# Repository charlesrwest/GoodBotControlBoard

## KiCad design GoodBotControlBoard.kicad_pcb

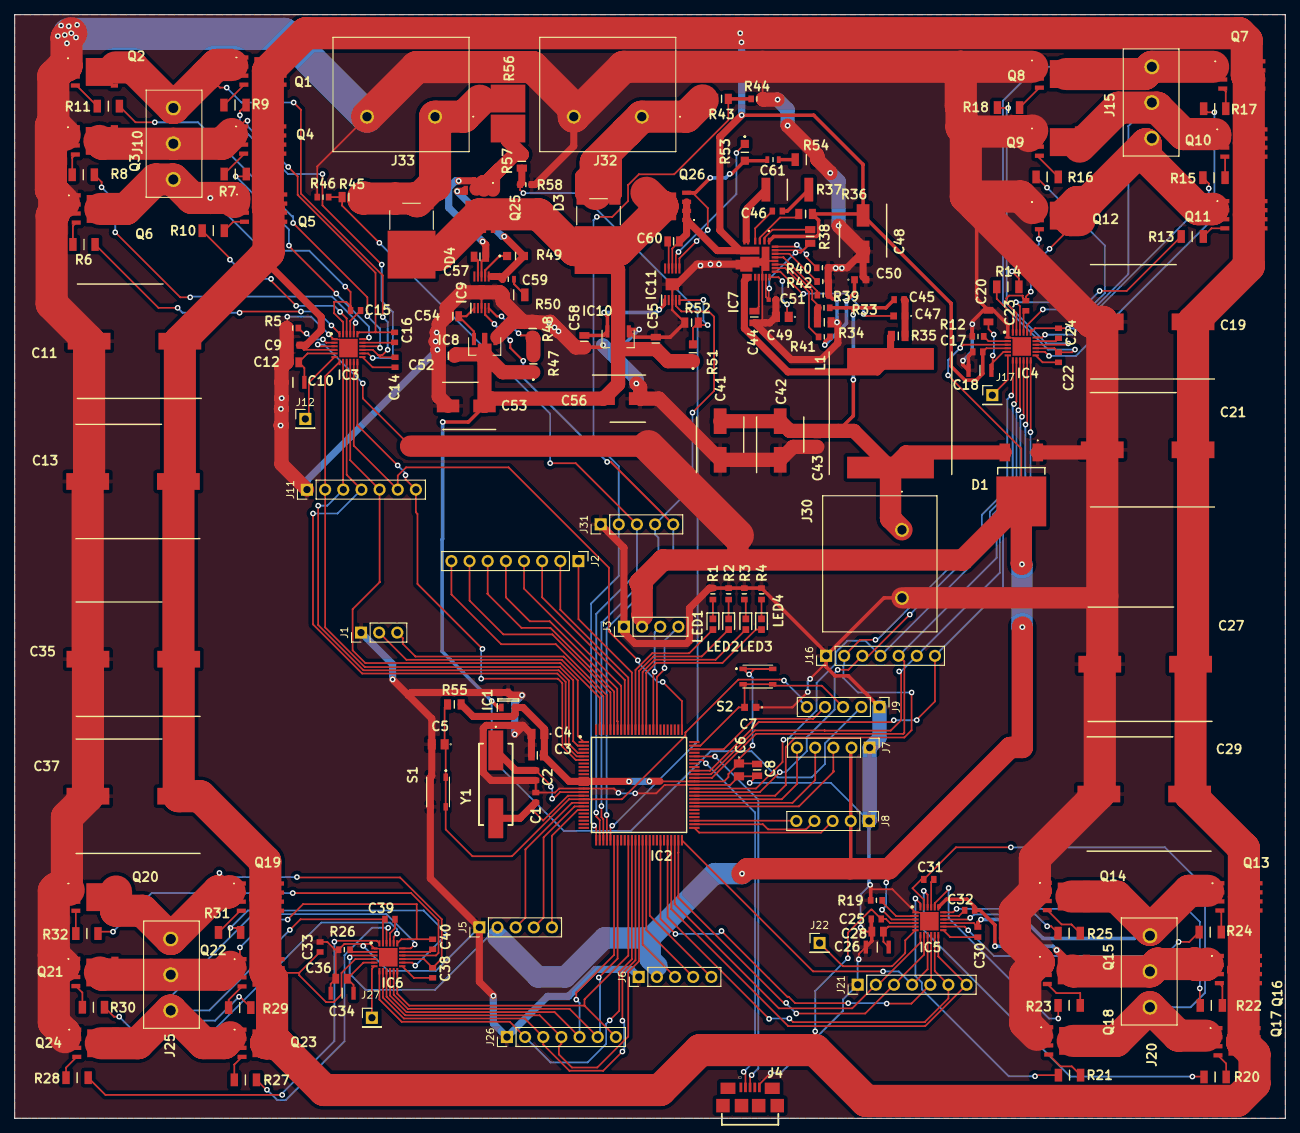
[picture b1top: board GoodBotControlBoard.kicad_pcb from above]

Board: 2 copper layers, 177.8 x 154.4 mm, 192 parts (0 on the bottom side), 190 nets.

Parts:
C1, C2, C9, C17, C25, C33, C43, C46: CL10B104KB8NNNC; CAPC1608X90N
C3, C8, C44, C52, C54, C55, C57, C58, C60: CL21A475KLCLQNC; CAPC2012X95N
C4, C5, C6, C49: C0805C333K1RECAUTO; C0805
C7, C50: C0603C471K2RACAUTO; C0603
C10, C18, C26, C34: C3216X5R1V226M160AC; CAPC3216X180N
C11, C13, C19, C21, C27, C29, C35, C37: 865080663020; CAPAE1600X1700N
C12, C20, C28, C36: 885012207100; CAPC2012X135N
C14, C15, C16, C22, C23, C24, C30, C31, C32, C38, C39, C40: GRM188R6YA225MA12D; CAPC1608X90N
C41, C42: 865080545011; CAPAE660X770N
C45: 06035C182KAT2A; CAPC1608X90N
C47: C0603C222J5RACAUTO; C0603
C48, C53, C56: 865080543009; CAPAE660X550N
C51: GRM155R61H105KE05D; CAPC1005X55N
C59, C61: C1608X7R1V474K080AE; CAPC1608X80N
D1: AZ1084CD-3.3TRG1; AZ1084CD33TRG1
D3, D4: FERD20H100SB-TR; FERD20H100SBTR
IC1: AP7375-33SA-7; SOT96P240X110-3N
IC2: STM32G0B1VET6; QFP50P1600X1600X160-100N
IC3, IC4, IC5, IC6: STDRIVE101; QFN50P400X400X100-25N-D
IC7: SiC462ED-T1-GE3; SiC462EDT1GE3
IC8, IC10: ZXTR2012Z-7; ZXTR2012Z7
IC9, IC11: LTC7004EMSE#PBF; SOP50P490X110-11N
J1: Conn_01x03_Socket; PinHeader_1x03_P2.54mm_Vertical
J2: Conn_01x08_Pin; PinHeader_1x08_P2.54mm_Vertical
J3: Conn_01x04_Socket; PinHeader_1x04_P2.54mm_Vertical
J4: 10118192-0001LF
J5, J6, J7, J8, J9: Conn_01x05_Socket; PinHeader_1x05_P2.54mm_Vertical
J10, J15, J20, J25: TB003-500-P03BE; TB003500P03BE
J11, J16, J21, J26: Conn_01x07_Pin; PinHeader_1x07_P2.54mm_Vertical
J12, J17, J22, J27: Conn_01x01_Pin; PinHeader_1x01_P2.54mm_Vertical
J30, J32, J33: 1902547
J31: Conn_01x05_Pin; PinHeader_1x05_P2.54mm_Vertical
L1: IHLP6767GZER4R7M11; INDPM172172X700N
LED1, LED2, LED3, LED4: 150060VS75000; LEDC1608X80N
Q1, Q2, Q3, Q4, Q5, Q6, Q7, Q8, Q9, Q10, Q11, Q12, Q13, Q14, Q15, Q16, Q17, Q18, Q19, Q20, Q21, Q22, Q23, Q24, Q25, Q26: SIR500DP-T1-RE3; SIR500DPT1RE3
R1, R2, R3, R4, R40: CRCW06032K00FKEAC; RESC1608X55N
R5, R12, R19, R26: CRCW0603200KFKEAC; RESC1608X55N
R6, R7, R8, R9, R10, R11, R13, R14, R15, R16, R17, R18, R20, R21, R22, R23, R24, R25, R27, R28, R29, R30, R31, R32, R50, R54: RK73B2BTTD100J; RESC3216X70N
R33, R39, R44, R46, R58: RC0603FR-1052K3L; RESC1608X55N
R34, R55: CRCW080510K0FKEAC; RESC2012X60N
R35: CR0805-FX-8661ELF; RESC2012X60N
R36, R43, R45, R57: CR0805-FX-5603ELF; RESC2012X60N
R37: CRCW25123R30FKEG; RESC6332X70N
R38: CR0805-FX-1023ELF; RESC2012X60N
R41: ERJ-3EKF2323V; RESC1608X55N
R42: RT0603CRE0760K4L; RESC1608X55N
R47, R49, R51, R53: ERJ-6ENF2213V; ERJ6ENF1000V
R48, R52: CR0805-FX-1212ELF; RESC2012X60N
R56: WSHP2818R1000FEB; RESC7146X175N
S1, S2: PTS810SJM250SMTRLFS; PTS810SJG250SMTRLFS
Y1: ABLS-8.000MHZ-B4-T; ABLS8000MHZB4T2

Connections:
+3.3V: D1.2 (OUTPUT), IC3.3 (SCREF), IC4.3 (SCREF), IC5.3 (SCREF), IC6.3 (SCREF), J3.2, J5.2, J6.2, J7.2, J8.2
+5V: C41.2, C42.2, C43.2, C45.1, D1.3 (INPUT), J30.1, L1.1, R33.2
+28V: C9.1, C11.1 (+), C13.1 (+), C17.1, C19.1 (+), C21.1 (+), C25.1, C27.1 (+), C29.1 (+), C33.1, C35.1 (+), C37.1 (+), C48.1 (+), C60.2, IC3.4 (VS), IC4.4 (VS), IC5.4 (VS), IC6.4 (VS), IC7.1 (VCIN), IC7.7 (VIN_1), IC7.8 (VIN_2), IC7.29 (VIN_3), IC11.8 (TS), Q1.5 (D_1), Q1.6 (D_2), Q1.7 (D_3), Q1.8 (D_4), Q1.9 (D_5), Q1.10 (D_6), Q1.11 (D_7), Q4.5 (D_1), Q4.6 (D_2), Q4.7 (D_3), Q4.8 (D_4), Q4.9 (D_5), Q4.10 (D_6), Q4.11 (D_7), Q5.5 (D_1), Q5.6 (D_2), Q5.7 (D_3), Q5.8 (D_4), Q5.9 (D_5), Q5.10 (D_6), Q5.11 (D_7), Q7.5 (D_1), Q7.6 (D_2), Q7.7 (D_3), Q7.8 (D_4), Q7.9 (D_5), Q7.10 (D_6), Q7.11 (D_7), Q10.5 (D_1), Q10.6 (D_2), Q10.7 (D_3), Q10.8 (D_4), Q10.9 (D_5), Q10.10 (D_6), Q10.11 (D_7), Q11.5 (D_1), Q11.6 (D_2), Q11.7 (D_3), Q11.8 (D_4), Q11.9 (D_5), Q11.10 (D_6), Q11.11 (D_7), Q13.5 (D_1), Q13.6 (D_2), Q13.7 (D_3), Q13.8 (D_4), Q13.9 (D_5), Q13.10 (D_6), Q13.11 (D_7), Q16.5 (D_1), Q16.6 (D_2), Q16.7 (D_3), Q16.8 (D_4), Q16.9 (D_5), Q16.10 (D_6), Q16.11 (D_7), Q17.5 (D_1), Q17.6 (D_2), Q17.7 (D_3), Q17.8 (D_4), Q17.9 (D_5), Q17.10 (D_6), Q17.11 (D_7), Q19.5 (D_1), Q19.6 (D_2), Q19.7 (D_3), Q19.8 (D_4), Q19.9 (D_5), Q19.10 (D_6), Q19.11 (D_7), Q22.5 (D_1), Q22.6 (D_2), Q22.7 (D_3), Q22.8 (D_4), Q22.9 (D_5), Q22.10 (D_6), Q22.11 (D_7), Q23.5 (D_1), Q23.6 (D_2), Q23.7 (D_3), Q23.8 (D_4), Q23.9 (D_5), Q23.10 (D_6), Q23.11 (D_7), Q26.1 (S_1), Q26.2 (S_2), Q26.3 (S_3), R36.1
BAT_CHARGE_ON: IC2.29 (PA4), IC9.4 (INP), J31.5
Battery+: D4.1 (A_1), D4.3 (A_2), J33.1, R45.2, R56.2
BatteryDiv+: IC2.27 (PA2), J31.3, R45.1, R46.1
CHARGER+: D3.1 (A_1), D3.3 (A_2), J32.1, R43.2
ChargerCurrent+: C57.2, IC9.8 (TS), Q25.1 (S_1), Q25.2 (S_2), Q25.3 (S_3), R56.1, R57.2
ChargerCurrentDiv+: IC2.30 (PA5), R57.1, R58.1
ChargerDiv+: IC2.26 (PA1), J31.2, R43.1, R44.1
GND: C1.1, C2.1, C3.2, C4.2, C5.2, C6.2, C7.1, C8.2, C9.2, C10.2, C11.2 (-), C12.2, C13.2 (-), C17.2, C18.2, C19.2 (-), C20.2, C21.2 (-), C25.2, C26.2, C27.2 (-), C28.2, C29.2 (-), C33.2, C34.2, C35.2 (-), C36.2, C37.2 (-), C41.1, C42.1, C43.1, C44.1, C48.2 (-), C49.2, C50.2, C51.2, C52.2, C53.2 (-), C54.2, C55.2, C56.2 (-), C58.2, D1.1 (ADJ/GND), IC1.3 (GND), IC2.14 (VSS/VSSA), IC2.63 (VSS), IC3.1 (CP), IC3.25 (GND), IC4.1 (CP), IC4.25 (GND), IC5.1 (CP), IC5.25 (GND), IC6.1 (CP), IC6.25 (GND), IC7.9 (PGND_1), IC7.10 (PGND_2), IC7.11 (PGND_3), IC7.17 (PGND_4), IC7.23 (AGND_1), IC7.28 (AGND_2), IC7.30 (PGND_5), IC7.31 (PGND_6), IC8.1 (GND), IC9.3 (GND_1), IC9.11 (GND_2), IC10.1 (GND), IC11.3 (GND_1), IC11.11 (GND_2), J1.1, J3.1, J4.5, J5.1, J6.1, J7.1, J8.1, J9.1, J11.1, J16.1, J21.1, J26.1, J30.2, J31.1, J32.2, J33.2, Q2.1 (S_1), Q2.2 (S_2), Q2.3 (S_3), Q3.1 (S_1), Q3.2 (S_2), Q3.3 (S_3), Q6.1 (S_1), Q6.2 (S_2), Q6.3 (S_3), Q8.1 (S_1), Q8.2 (S_2), Q8.3 (S_3), Q9.1 (S_1), Q9.2 (S_2), Q9.3 (S_3), Q12.1 (S_1), Q12.2 (S_2), Q12.3 (S_3), Q14.1 (S_1), Q14.2 (S_2), Q14.3 (S_3), Q15.1 (S_1), Q15.2 (S_2), Q15.3 (S_3), Q18.1 (S_1), Q18.2 (S_2), Q18.3 (S_3), Q20.1 (S_1), Q20.2 (S_2), Q20.3 (S_3), Q21.1 (S_1), Q21.2 (S_2), Q21.3 (S_3), Q24.1 (S_1), Q24.2 (S_2), Q24.3 (S_3), R1.1, R2.1, R3.1, R4.1, R5.1, R12.1, R19.1, R26.1, R34.1, R39.2, R40.2, R42.2, R44.2, R46.2, R48.2, R50.2, R52.2, R54.2, R58.2, S1.3, S1.4
M0_BOOT1: C15.1, IC3.21 (BOOT1)
M0_BOOT2: C16.1, IC3.17 (BOOT2)
M0_BOOT3: C14.1, IC3.13 (BOOT3)
M0_EN1: IC2.1 (PB9), IC3.10 (INL1/EN1), J11.5
M0_EN2: IC2.76 (PC8), IC3.11 (INL2/EN2), J11.6
M0_EN3: IC2.6 (PE6), IC3.12 (INL3/EN3), J11.7
M0_GHS1: IC3.22 (GHS1), R10.1
M0_GHS2: IC3.18 (GHS2), R7.1
M0_GHS3: IC3.14 (GHS3), R9.1
M0_GLS1: IC3.24 (GLS1), R6.1
M0_GLS2: IC3.20 (GLS2), R8.1
M0_GLS3: IC3.16 (GLS3), R11.1
M0_HALL1: IC2.18 (PF3), J5.3
M0_HALL2: IC2.19 (PF4), J5.4
M0_HALL3: IC2.20 (PF5), J5.5
M0_IN1: IC2.2 (PC10), IC3.7 (INH1/IN1), J11.2
M0_IN2: IC2.4 (PE4), IC3.8 (INH2/IN2), J11.3
M0_IN3: IC2.5 (PE5), IC3.9 (INH3/IN3), J11.4
M0_MOTOR_U: C15.2, IC3.23 (OUT1), J10.3, Q5.1 (S_1), Q5.2 (S_2), Q5.3 (S_3), Q6.5 (D_1), Q6.6 (D_2), Q6.7 (D_3), Q6.8 (D_4), Q6.9 (D_5), Q6.10 (D_6), Q6.11 (D_7)
M0_MOTOR_V: C16.2, IC3.19 (OUT2), J10.2, Q3.5 (D_1), Q3.6 (D_2), Q3.7 (D_3), Q3.8 (D_4), Q3.9 (D_5), Q3.10 (D_6), Q3.11 (D_7), Q4.1 (S_1), Q4.2 (S_2), Q4.3 (S_3)
M0_MOTOR_W: C14.2, IC3.15 (OUT3), J10.1, Q1.1 (S_1), Q1.2 (S_2), Q1.3 (S_3), Q2.5 (D_1), Q2.6 (D_2), Q2.7 (D_3), Q2.8 (D_4), Q2.9 (D_5), Q2.10 (D_6), Q2.11 (D_7)
M1_BOOT1: C23.1, IC4.21 (BOOT1)
M1_BOOT2: C24.1, IC4.17 (BOOT2)
M1_BOOT3: C22.1, IC4.13 (BOOT3)
M1_EN1: IC2.65 (PD12), IC4.10 (INL1/EN1), J16.5
M1_EN2: IC2.66 (PD13), IC4.11 (INL2/EN2), J16.6
M1_EN3: IC2.67 (PD14), IC4.12 (INL3/EN3), J16.7
M1_GHS1: IC4.22 (GHS1), R13.1
M1_GHS2: IC4.18 (GHS2), R15.1
M1_GHS3: IC4.14 (GHS3), R17.1
M1_GLS1: IC4.24 (GLS1), R14.1
M1_GLS2: IC4.20 (GLS2), R16.1
M1_GLS3: IC4.16 (GLS3), R18.1
M1_HALL1: IC2.57 (PC6), J7.3
M1_HALL2: IC2.58 (PC7), J7.4
M1_HALL3: IC2.59 (PD8), J7.5
M1_IN1: IC2.60 (PD9), IC4.7 (INH1/IN1), J16.2
M1_IN2: IC2.61 (PD10), IC4.8 (INH2/IN2), J16.3
M1_IN3: IC2.62 (PD11), IC4.9 (INH3/IN3), J16.4
M1_MOTOR_U: C23.2, IC4.23 (OUT1), J15.1, Q11.1 (S_1), Q11.2 (S_2), Q11.3 (S_3), Q12.5 (D_1), Q12.6 (D_2), Q12.7 (D_3), Q12.8 (D_4), Q12.9 (D_5), Q12.10 (D_6), Q12.11 (D_7)
M1_MOTOR_V: C24.2, IC4.19 (OUT2), J15.2, Q9.5 (D_1), Q9.6 (D_2), Q9.7 (D_3), Q9.8 (D_4), Q9.9 (D_5), Q9.10 (D_6), Q9.11 (D_7), Q10.1 (S_1), Q10.2 (S_2), Q10.3 (S_3)
M1_MOTOR_W: C22.2, IC4.15 (OUT3), J15.3, Q7.1 (S_1), Q7.2 (S_2), Q7.3 (S_3), Q8.5 (D_1), Q8.6 (D_2), Q8.7 (D_3), Q8.8 (D_4), Q8.9 (D_5), Q8.10 (D_6), Q8.11 (D_7)
M2_BOOT1: C31.1, IC5.21 (BOOT1)
M2_BOOT2: C32.1, IC5.17 (BOOT2)
M2_BOOT3: C30.1, IC5.13 (BOOT3)
M2_EN1: IC2.44 (PE11), IC5.10 (INL1/EN1), J21.5
M2_EN2: IC2.46 (PE13), IC5.11 (INL2/EN2), J21.6
M2_EN3: IC2.47 (PE14), IC5.12 (INL3/EN3), J21.7
M2_GHS1: IC5.22 (GHS1), R20.1
M2_GHS2: IC5.18 (GHS2), R22.1
M2_GHS3: IC5.14 (GHS3), R24.1
M2_GLS1: IC5.24 (GLS1), R21.1
M2_GLS2: IC5.20 (GLS2), R23.1
M2_GLS3: IC5.16 (GLS3), R25.1
M2_HALL1: IC2.51 (PB12), J8.3
M2_HALL2: IC2.52 (PB13), J8.4
M2_HALL3: IC2.53 (PB14), J8.5
M2_IN1: IC2.48 (PE15), IC5.7 (INH1/IN1), J21.2
M2_IN2: IC2.49 (PB10), IC5.8 (INH2/IN2), J21.3
M2_IN3: IC2.50 (PB11), IC5.9 (INH3/IN3), J21.4
M2_MOTOR_U: C31.2, IC5.23 (OUT1), J20.1, Q17.1 (S_1), Q17.2 (S_2), Q17.3 (S_3), Q18.5 (D_1), Q18.6 (D_2), Q18.7 (D_3), Q18.8 (D_4), Q18.9 (D_5), Q18.10 (D_6), Q18.11 (D_7)
M2_MOTOR_V: C32.2, IC5.19 (OUT2), J20.2, Q15.5 (D_1), Q15.6 (D_2), Q15.7 (D_3), Q15.8 (D_4), Q15.9 (D_5), Q15.10 (D_6), Q15.11 (D_7), Q16.1 (S_1), Q16.2 (S_2), Q16.3 (S_3)
M2_MOTOR_W: C30.2, IC5.15 (OUT3), J20.3, Q13.1 (S_1), Q13.2 (S_2), Q13.3 (S_3), Q14.5 (D_1), Q14.6 (D_2), Q14.7 (D_3), Q14.8 (D_4), Q14.9 (D_5), Q14.10 (D_6), Q14.11 (D_7)
M3_BOOT1: C39.1, IC6.21 (BOOT1)
M3_BOOT2: C40.1, IC6.17 (BOOT2)
M3_BOOT3: C38.1, IC6.13 (BOOT3)
M3_EN1: IC2.31 (PA6), IC6.10 (INL1/EN1), J26.5
M3_EN2: IC2.32 (PA7), IC6.11 (INL2/EN2), J26.6
M3_EN3: IC2.35 (PB0), IC6.12 (INL3/EN3), J26.7
M3_GHS1: IC6.22 (GHS1), R27.1
M3_GHS2: IC6.18 (GHS2), R29.1
M3_GHS3: IC6.14 (GHS3), R31.1
M3_GLS1: IC6.24 (GLS1), R28.1
M3_GLS2: IC6.20 (GLS2), R30.1
M3_GLS3: IC6.16 (GLS3), R32.1
M3_HALL1: IC2.39 (PF7), J6.3
M3_HALL2: IC2.40 (PE7), J6.4
M3_HALL3: IC2.41 (PE8), J6.5
M3_IN1: IC2.36 (PB1), IC6.7 (INH1/IN1), J26.2
M3_IN2: IC2.37 (PB2), IC6.8 (INH2/IN2), J26.3
M3_IN3: IC2.38 (PF6), IC6.9 (INH3/IN3), J26.4
M3_MOTOR_U: C39.2, IC6.23 (OUT1), J25.3, Q23.1 (S_1), Q23.2 (S_2), Q23.3 (S_3), Q24.5 (D_1), Q24.6 (D_2), Q24.7 (D_3), Q24.8 (D_4), Q24.9 (D_5), Q24.10 (D_6), Q24.11 (D_7)
M3_MOTOR_V: C40.2, IC6.19 (OUT2), J25.2, Q21.5 (D_1), Q21.6 (D_2), Q21.7 (D_3), Q21.8 (D_4), Q21.9 (D_5), Q21.10 (D_6), Q21.11 (D_7), Q22.1 (S_1), Q22.2 (S_2), Q22.3 (S_3)
M3_MOTOR_W: C38.2, IC6.15 (OUT3), J25.1, Q19.1 (S_1), Q19.2 (S_2), Q19.3 (S_3), Q20.5 (D_1), Q20.6 (D_2), Q20.7 (D_3), Q20.8 (D_4), Q20.9 (D_5), Q20.10 (D_6), Q20.11 (D_7)
MAIN_POWER_ON: IC2.28 (PA3), IC11.4 (INP), J31.4
MCU_LED1: IC2.86 (PF9), LED4.2 (A)
MCU_LED2: IC2.87 (PF10), LED3.2 (A)
MCU_LED3: IC2.88 (PF11), LED2.2 (A)
MCU_LED4: IC2.89 (PF12), LED1.2 (A)
MCU_NRST: C5.1, IC2.17 (PF2-NRST), J9.5, R55.2, S1.1, S1.2
MCU_VDD: C3.1, C4.1, C6.1, C8.1, IC1.2 (VOUT), IC2.11 (VBAT), IC2.12 (VREF+), IC2.13 (VDD/VDDA), IC2.64 (VDDIO2), R55.1, S2.1, S2.2
unnamed: C45.2, C47.1, R35.1
unnamed: C46.2, R37.1
unnamed: C50.1, R41.2
unnamed: C59.1, R50.1
unnamed: C61.1, R54.1
unnamed: IC2.91 (PB3), J2.2
unnamed: IC2.92 (PB4), J2.3
unnamed: IC2.93 (PB5), J2.4
unnamed: IC2.94 (PE0), J2.5
unnamed: IC2.95 (PE1), J2.6
unnamed: IC2.96 (PE2), J2.7
unnamed: IC2.97 (PE3), J2.8
unnamed: C2.2, IC2.15 (PF0-OSC_IN), Y1.1
unnamed: C1.2, IC2.16 (PF1-OSC_OUT), Y1.2
unnamed: IC2.90 (PF13), J2.1
unnamed: IC3.2 (DT/MODE), R5.2
unnamed: IC3.6 (NFAULT), J12.1
unnamed: C10.1, C12.1, IC3.5 (REG12)
unnamed: IC4.2 (DT/MODE), R12.2
unnamed: IC4.6 (NFAULT), J17.1
unnamed: C18.1, C20.1, IC4.5 (REG12)
unnamed: IC5.2 (DT/MODE), R19.2
unnamed: IC5.6 (NFAULT), J22.1
unnamed: C26.1, C28.1, IC5.5 (REG12)
unnamed: IC6.2 (DT/MODE), R26.2
unnamed: IC6.6 (NFAULT), J27.1
unnamed: C34.1, C36.1, IC6.5 (REG12)
unnamed: C46.1, IC7.4 (BOOT)
unnamed: IC7.21 (COMP), R41.1
unnamed: IC7.3 (EN), R36.2
unnamed: IC7.24 (FSW), R39.1
unnamed: IC7.25 (ILIM), R42.1
unnamed: IC7.27 (MODE), R40.1
unnamed: IC7.2 (PGOOD), R38.2
unnamed: IC7.5 (PHASE_1), IC7.6 (PHASE_2), R37.2
unnamed: C49.1, IC7.19 (SS)
unnamed: IC7.12 (SW_1), IC7.13 (SW_2), IC7.14 (SW_3), IC7.32 (SW_4), L1.2, R35.2
unnamed: C51.1, IC7.18 (ULTRASONIC), IC7.26 (VDD), R38.1
unnamed: C44.2, IC7.16 (VDRV)
unnamed: IC7.22 (VFB), R33.1, R34.2
unnamed: C47.2, IC7.20 (VSNS)
unnamed: C54.1, IC8.3 (VOUT), IC9.1 (VCC)
unnamed: C57.1, IC9.9 (BST)
unnamed: IC9.5 (OVLO), R47.2, R48.1
unnamed: C59.2, IC9.6 (TGDN), Q25.4 (G), R49.2
unnamed: IC9.7 (TGUP), R49.1
unnamed: C58.1, IC10.3 (VOUT), IC11.1 (VCC)
unnamed: C60.1, IC11.9 (BST)
unnamed: IC11.5 (OVLO), R51.2, R52.1
unnamed: C61.2, IC11.6 (TGDN), Q26.4 (G), R53.2
unnamed: IC11.7 (TGUP), R53.1
unnamed: LED1.1 (K), R1.2
unnamed: LED2.1 (K), R2.2
unnamed: LED3.1 (K), R3.2
unnamed: LED4.1 (K), R4.2
unnamed: Q1.4 (G), R9.2
unnamed: Q2.4 (G), R11.2
unnamed: Q3.4 (G), R8.2
unnamed: Q4.4 (G), R7.2
unnamed: Q5.4 (G), R10.2
unnamed: Q6.4 (G), R6.2
unnamed: Q7.4 (G), R17.2
unnamed: Q8.4 (G), R18.2
unnamed: Q9.4 (G), R16.2
unnamed: Q10.4 (G), R15.2
unnamed: Q11.4 (G), R13.2
unnamed: Q12.4 (G), R14.2
unnamed: Q13.4 (G), R24.2
unnamed: Q14.4 (G), R25.2
unnamed: Q15.4 (G), R23.2
unnamed: Q16.4 (G), R22.2
unnamed: Q17.4 (G), R20.2
unnamed: Q18.4 (G), R21.2
unnamed: Q19.4 (G), R31.2
unnamed: Q20.4 (G), R32.2
unnamed: Q21.4 (G), R30.2
unnamed: Q22.4 (G), R29.2
unnamed: Q23.4 (G), R27.2
unnamed: Q24.4 (G), R28.2
PowerIn+: C52.1, C53.1 (+), C55.1, C56.1 (+), D3.2 (K), D4.2 (K), IC1.1 (VIN), IC8.2 (VIN_1), IC8.4 (VIN_2), IC10.2 (VIN_1), IC10.4 (VIN_2), J9.2, Q25.5 (D_1), Q25.6 (D_2), Q25.7 (D_3), Q25.8 (D_4), Q25.9 (D_5), Q25.10 (D_6), Q25.11 (D_7), Q26.5 (D_1), Q26.6 (D_2), Q26.7 (D_3), Q26.8 (D_4), Q26.9 (D_5), Q26.10 (D_6), Q26.11 (D_7), R47.1, R51.1
SWCLK_BOOT: C7.2, IC2.74 (PA14-BOOT0), J9.3, S2.3, S2.4
SWDIO: IC2.73 (PA13), J9.4
USART1_RX: IC2.99 (PB7), J1.2
USART1_TX: IC2.98 (PB6), J1.3
USART2_RX: IC2.84 (PD6), J3.3
USART2_TX: IC2.83 (PD5), J3.4
USB_DM: IC2.70 (PA11_[PA9]), J4.2
USB_DP: IC2.71 (PA12_[PA10]), J4.3

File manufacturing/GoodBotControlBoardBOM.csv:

"Id";"Designator";"Footprint";"Quantity";"Designation";"Supplier and ref";
1;"L1";"INDPM172172X700N";1;"IHLP6767GZER4R7M11";;;
2;"R58,R39,R46,R33,R44";"RESC1608X55N";5;"RC0603FR-1052K3L";;;
3;"R57,R43,R36,R45";"RESC2012X60N";4;"CR0805-FX-5603ELF";;;
4;"R56";"RESC7146X175N";1;"WSHP2818R1000FEB";;;
5;"R55,R34";"RESC2012X60N";2;"CRCW080510K0FKEAC";;;
6;"R32,R31,R30,R29,R28,R27,R25,R24,R23,R22,R21,R20,R18,R17,R16,R15,R14,R13,R11,R10,R9,R8,R7,R6,R50,R54";"RESC3216X70N";26;"RK73B2BTTD100J";;;
7;"J31";"PinHeader_1x05_P2.54mm_Vertical";1;"Conn_01x05_Pin";;;
8;"J26,J21,J16,J11";"PinHeader_1x07_P2.54mm_Vertical";4;"Conn_01x07_Pin";;;
9;"J9,J8,J7,J6,J5";"PinHeader_1x05_P2.54mm_Vertical";5;"Conn_01x05_Socket";;;
10;"J3";"PinHeader_1x04_P2.54mm_Vertical";1;"Conn_01x04_Socket";;;
11;"J2";"PinHeader_1x08_P2.54mm_Vertical";1;"Conn_01x08_Pin";;;
12;"J1";"PinHeader_1x03_P2.54mm_Vertical";1;"Conn_01x03_Socket";;;
13;"C7,C50";"C0603";2;"C0603C471K2RACAUTO";;;
14;"C24,C31,C15,C30,C32,C14,C16,C40,C23,C39,C38,C22";"CAPC1608X90N";12;"GRM188R6YA225MA12D";;;
15;"R5,R26,R19,R12";"RESC1608X55N";4;"CRCW0603200KFKEAC";;;
16;"C58,C60,C8,C44,C55,C3,C54,C57,C52";"CAPC2012X95N";9;"CL21A475KLCLQNC";;;
17;"C41,C42";"CAPAE660X770N";2;"865080545011";;;
18;"C28,C12,C20,C36";"CAPC2012X135N";4;"885012207100";;;
19;"C10,C34,C26,C18";"CAPC3216X180N";4;"C3216X5R1V226M160AC";;;
20;"R37";"RESC6332X70N";1;"CRCW25123R30FKEG";;;
21;"IC7";"SiC462EDT1GE3";1;"SiC462ED-T1-GE3";;;
22;"R41";"RESC1608X55N";1;"ERJ-3EKF2323V";;;
23;"C51";"CAPC1005X55N";1;"GRM155R61H105KE05D";;;
24;"R3,R4,R2,R1,R40";"RESC1608X55N";5;"CRCW06032K00FKEAC";;;
25;"IC5,IC3,IC6,IC4";"QFN50P400X400X100-25N-D";4;"STDRIVE101";;;
26;"IC11,IC9";"SOP50P490X110-11N";2;"LTC7004EMSE#PBF";;;
27;"J17,J27,J12,J22";"PinHeader_1x01_P2.54mm_Vertical";4;"Conn_01x01_Pin";;;
28;"Q7,Q4,Q18,Q5,Q23,Q21,Q2,Q20,Q22,Q17,Q1,Q11,Q6,Q8,Q9,Q14,Q19,Q13,Q26,Q25,Q12,Q15,Q3,Q10,Q16,Q24";"SIR500DPT1RE3";26;"SIR500DP-T1-RE3";;;
29;"IC8,IC10";"ZXTR2012Z7";2;"ZXTR2012Z-7";;;
30;"LED2,LED1,LED4,LED3";"LEDC1608X80N";4;"150060VS75000";;;
31;"C29,C37,C21,C19,C35,C13,C11,C27";"CAPAE1600X1700N";8;"865080663020";;;
32;"C53,C56,C48";"CAPAE660X550N";3;"865080543009";;;
33;"C5,C4,C6,C49";"C0805";4;"C0805C333K1RECAUTO";;;
34;"J25,J10,J20,J15";"TB003500P03BE";4;"TB003-500-P03BE";;;
35;"S1,S2";"PTS810SJG250SMTRLFS";2;"PTS810SJM250SMTRLFS";;;
36;"R35";"RESC2012X60N";1;"CR0805-FX-8661ELF";;;
37;"C45";"CAPC1608X90N";1;"06035C182KAT2A";;;
38;"IC1";"SOT96P240X110-3N";1;"AP7375-33SA-7";;;
39;"J32,J33,J30";"1902547";3;"1902547";;;
40;"R53,R47,R51,R49";"ERJ6ENF1000V";4;"ERJ-6ENF2213V";;;
41;"R38";"RESC2012X60N";1;"CR0805-FX-1023ELF";;;
42;"C46,C1,C9,C17,C33,C25,C43,C2";"CAPC1608X90N";8;"CL10B104KB8NNNC";;;
43;"D4,D3";"FERD20H100SBTR";2;"FERD20H100SB-TR";;;
44;"Y1";"ABLS8000MHZB4T2";1;"ABLS-8.000MHZ-B4-T";;;
45;"C61,C59";"CAPC1608X80N";2;"C1608X7R1V474K080AE";;;
46;"R48,R52";"RESC2012X60N";2;"CR0805-FX-1212ELF";;;
47;"IC2";"QFP50P1600X1600X160-100N";1;"STM32G0B1VET6";;;
48;"D1";"AZ1084CD33TRG1";1;"AZ1084CD-3.3TRG1";;;
49;"C47";"C0603";1;"C0603C222J5RACAUTO";;;
50;"J4";"10118192-0001LF";1;"10118192-0001LF";;;
51;"R42";"RESC1608X55N";1;"RT0603CRE0760K4L";;;

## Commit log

2023-07-27 About to start wiring up the board.
2023-11-02 Starting work on the second version of the PCB design.
2023-11-09 Second version of board.
2024-03-24 The current version of the board with a physical implementation. About to get a redesign.
